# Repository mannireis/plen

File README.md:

# plen
A plen PCB for solder &lt;3. :3

This is a plen pcb that blinks the led every some seconds!

~~I made this to get a scrappy cat pfp from @acon!~~

This took me about 3-5 hours because i was learning how a Astable Multivibrator Circuits works!!

Schematic:

PCB:

BOM:

| Item             | Quantity | Price (USD) |
|------------------|----------|-------------|
| PCB              | 1        | 11.28       |
| PNP Transistors  | 2        | Kit         |
| LEDs             | 2        | Kit         |
| Battery Holder   | 1        | Kit         |
| Capacitors       | 2        | Kit         |
| Resistors        | 4        | Kit         |

This was a fun little pcb!!!

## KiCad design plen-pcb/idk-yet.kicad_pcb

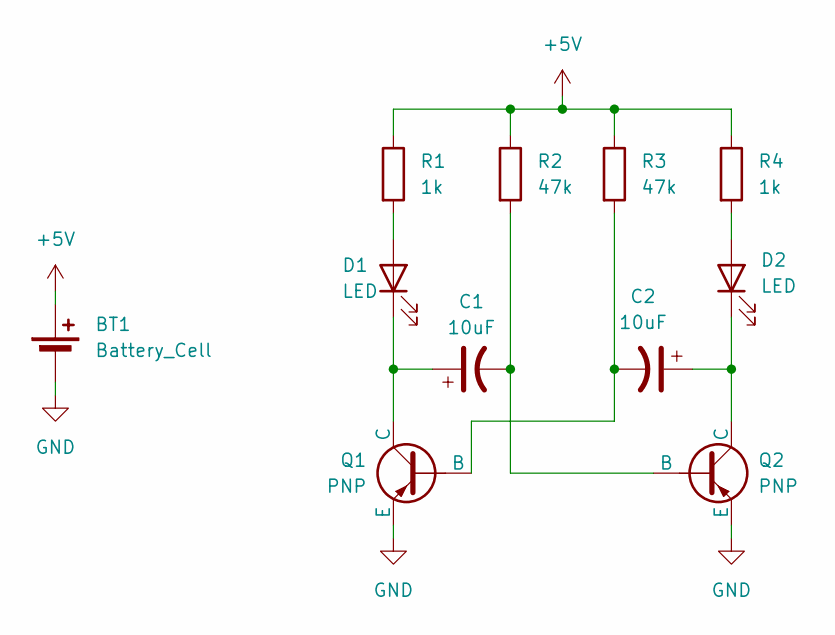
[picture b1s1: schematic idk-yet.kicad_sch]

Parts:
BT1: Battery_Cell; BatteryHolder_Keystone_3034_1x20mm
C1, C2: 10uF; CP_Radial_D8.0mm_P5.00mm
D1, D2: LED; LED_D5.0mm
Q1, Q2: PNP; TO-92L_HandSolder
R1, R4: 1k; R_Axial_DIN0207_L6.3mm_D2.5mm_P7.62mm_Horizontal
R2, R3: 47k; R_Axial_DIN0207_L6.3mm_D2.5mm_P7.62mm_Horizontal

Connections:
+5V: BT1.1 (+), R1.1, R2.1, R3.1, R4.1
GND: BT1.2 (-), Q1.3 (E), Q2.3 (E)
unnamed: D1.2 (A), R1.2
unnamed: C1.1, D1.1 (K), Q1.1 (C)
unnamed: D2.2 (A), R4.2
unnamed: C2.1, D2.1 (K), Q2.1 (C)
unnamed: C2.2, Q1.2 (B), R3.2
unnamed: C1.2, Q2.2 (B), R2.2

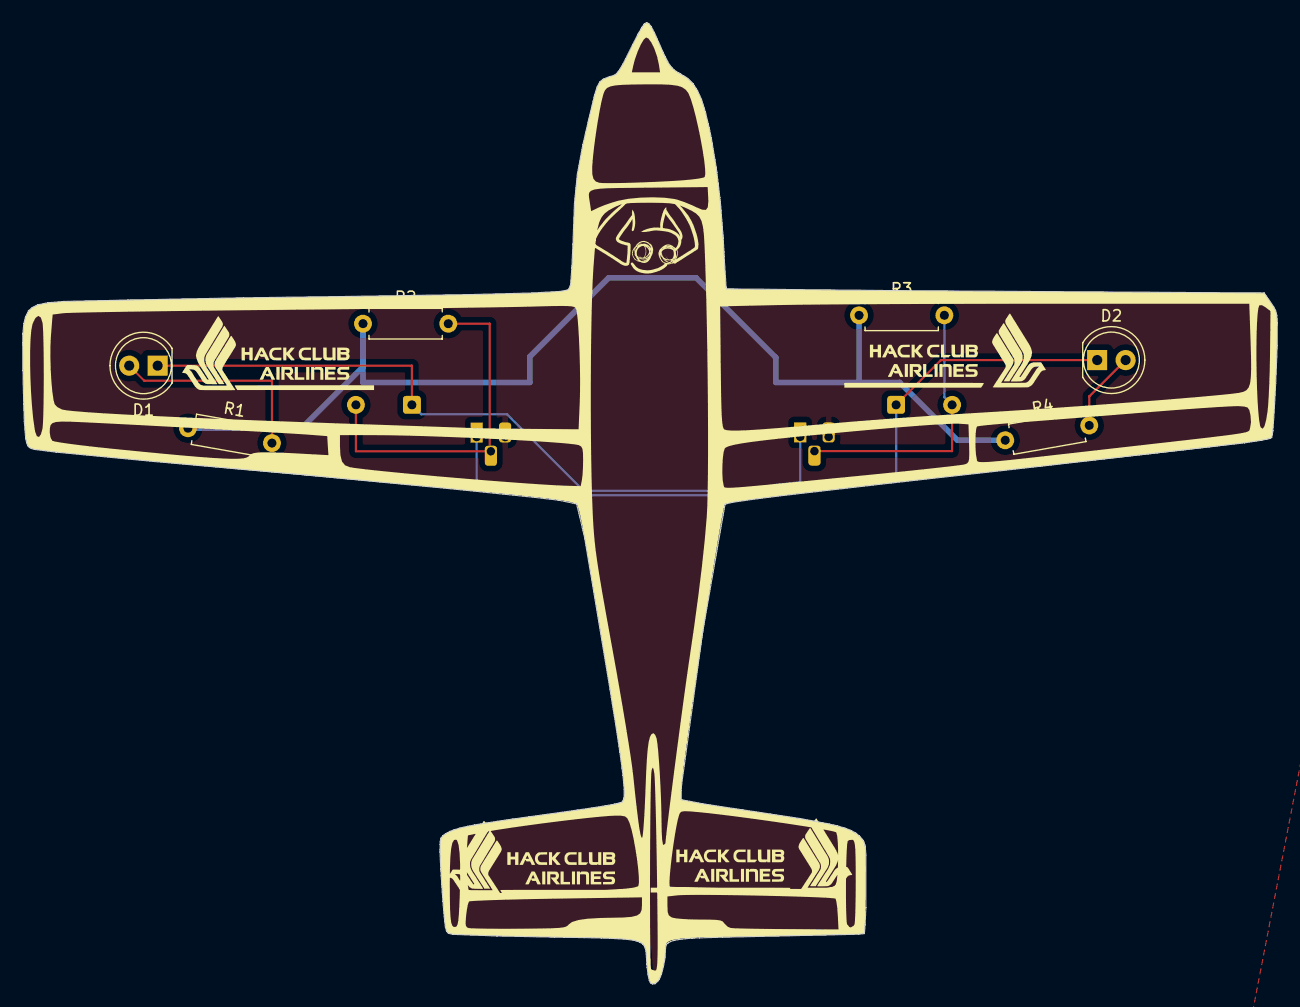
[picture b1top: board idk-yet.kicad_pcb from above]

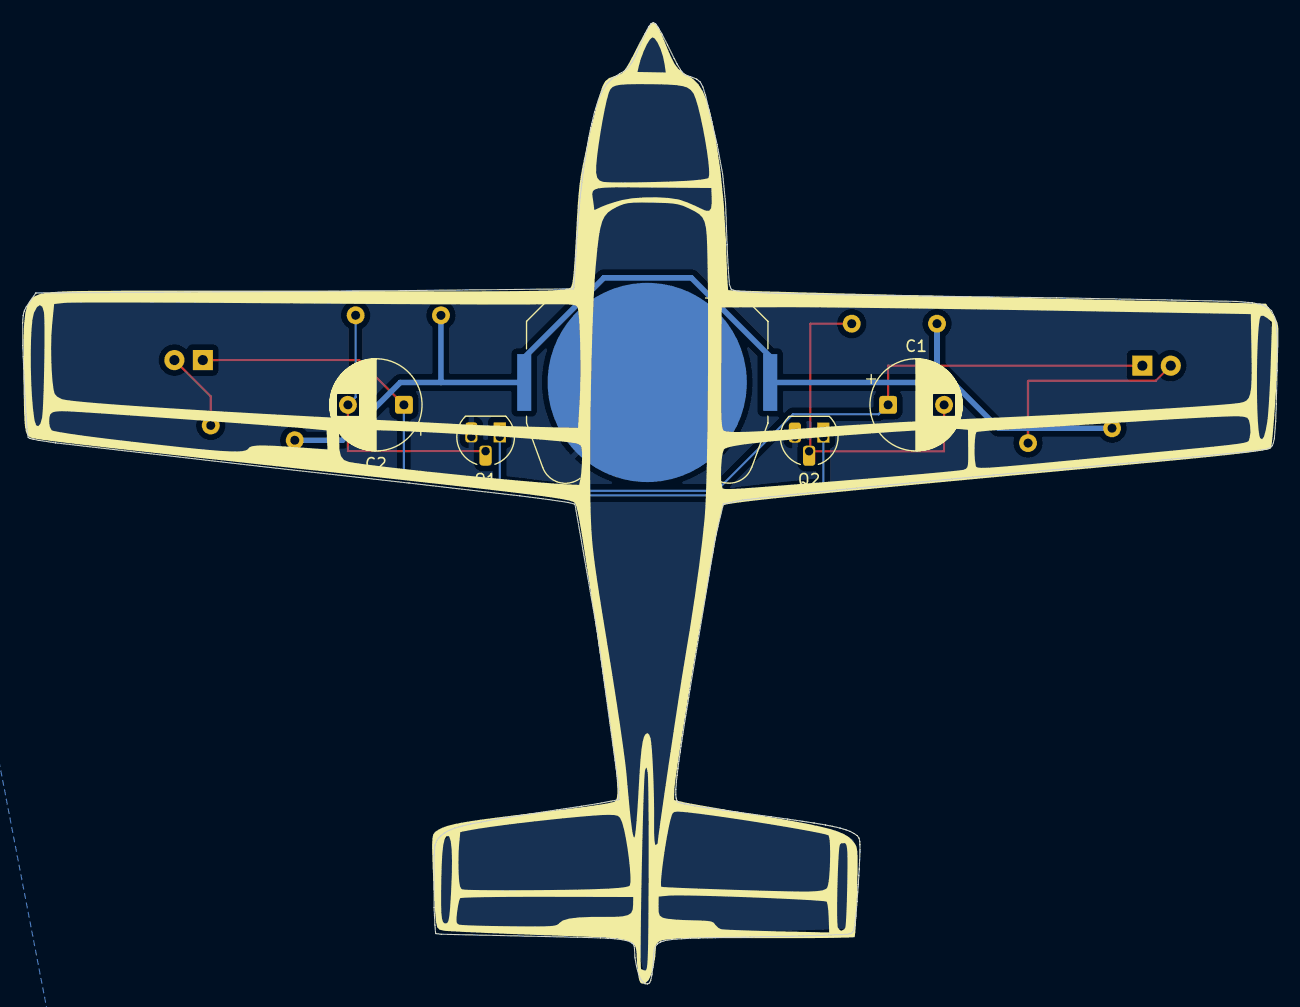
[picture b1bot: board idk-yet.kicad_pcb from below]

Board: 2 copper layers, 112.1 x 85.9 mm, 11 parts (5 on the bottom side), 8 nets.

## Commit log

2025-06-25 add pcb!
    :3
